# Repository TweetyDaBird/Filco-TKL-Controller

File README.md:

# Filco TKL Replacement Controller
 A QMK compatible drop-in replacement controller

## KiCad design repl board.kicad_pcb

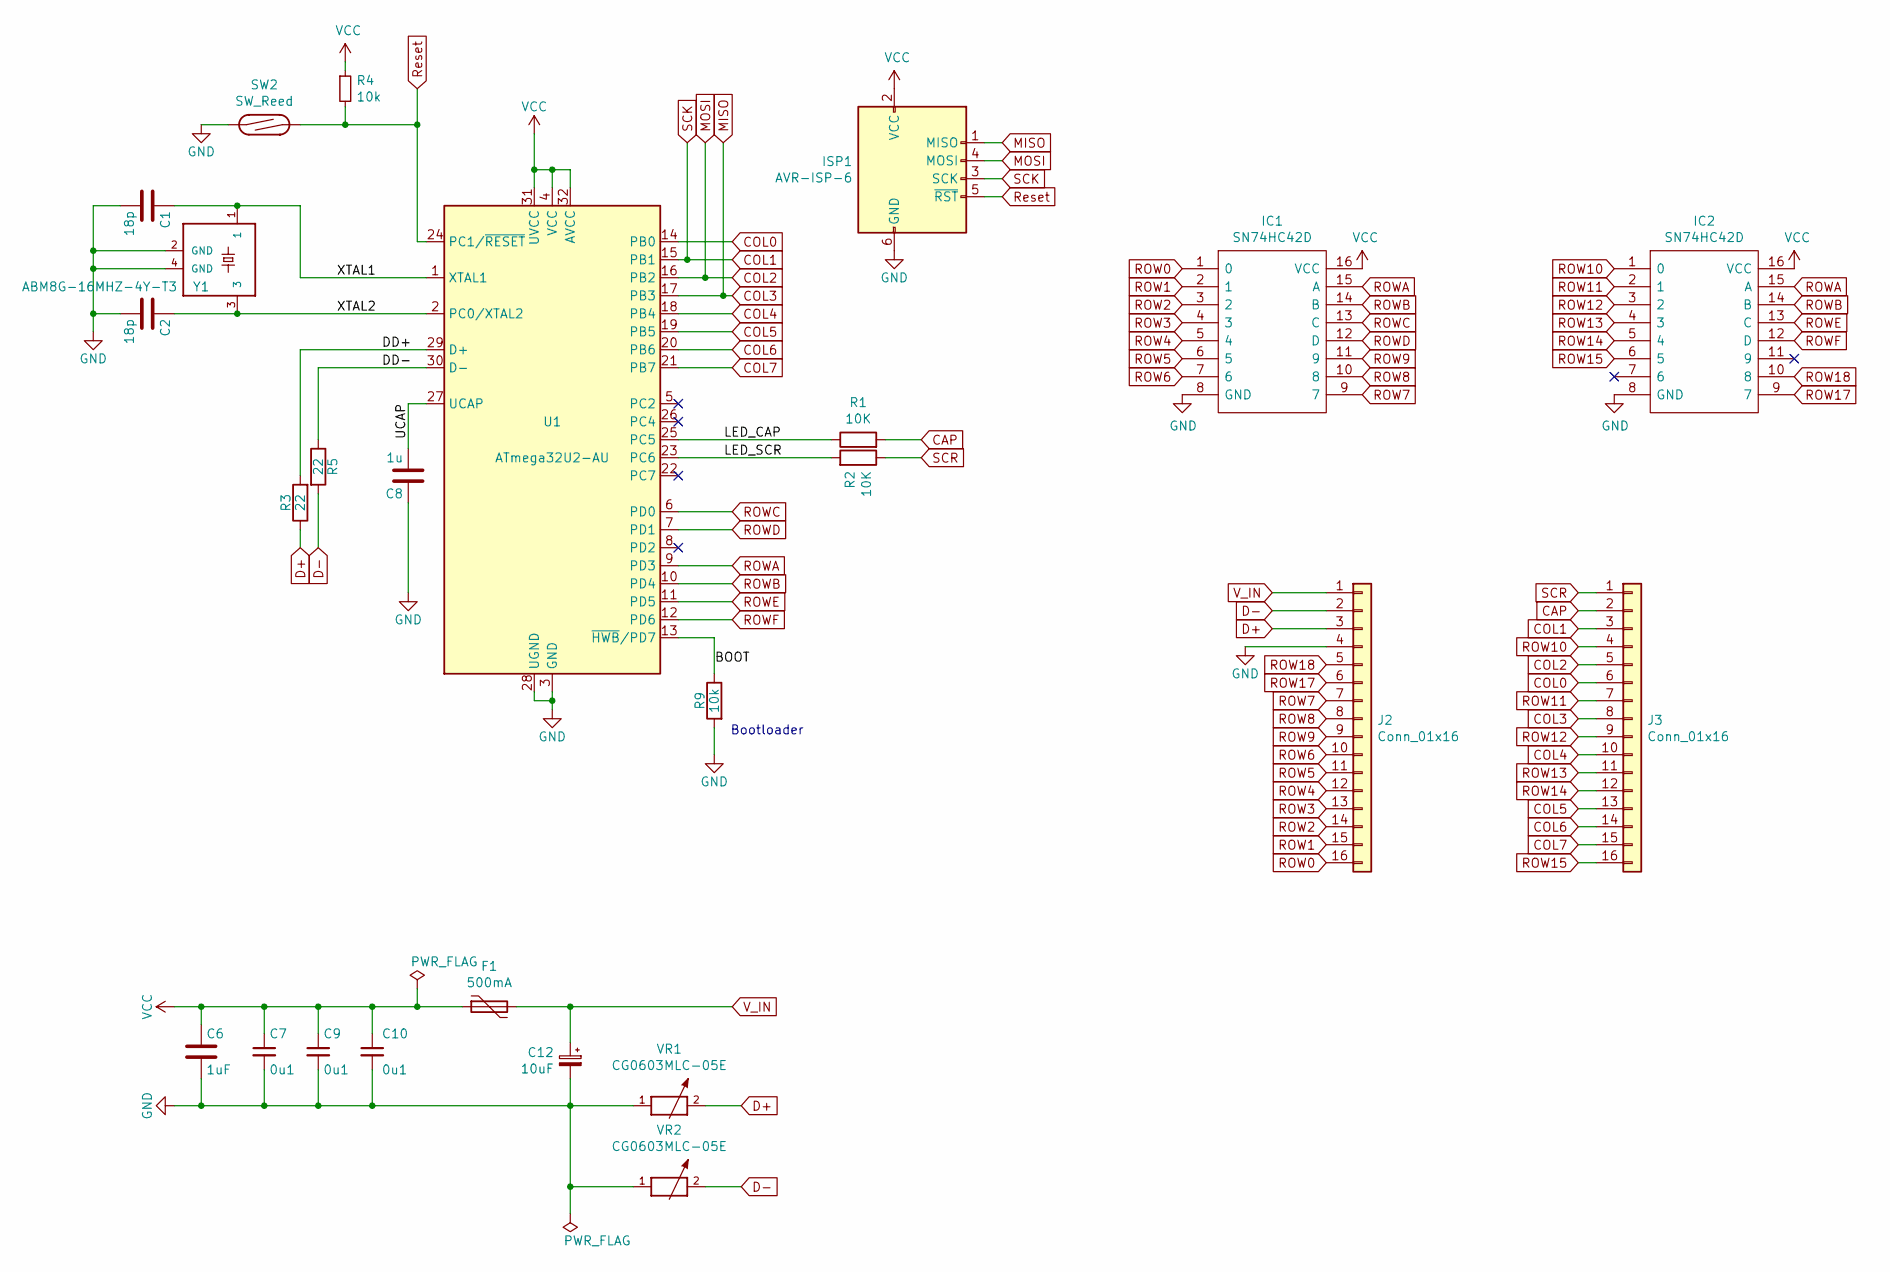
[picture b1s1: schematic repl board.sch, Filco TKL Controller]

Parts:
C1, C2: 18p; C_0603_1608Metric_Pad1.05x0.95mm_HandSolder
C6: 1uF; C_0603_1608Metric_Pad1.05x0.95mm_HandSolder
C7, C9, C10: 0u1; C_0603_1608Metric_Pad1.05x0.95mm_HandSolder
C8: 1u; C_0603_1608Metric_Pad1.05x0.95mm_HandSolder
C12: 10uF; CP_EIA-3216-18_Kemet-A_Pad1.58x1.35mm_HandSolder
F1: 500mA; Fuse_0805_2012Metric_Pad1.15x1.40mm_HandSolder
IC1, IC2: SN74HC42D; SOP-16_4.4x10.4mm_P1.27mm; Manufacturer_Part_Number SN74HC42D; Mouser Part Number 595-SN74HC42D
ISP1: AVR-ISP-6; PinHeader_1x06_P2.54mm_Vertical
J2, J3: Conn_01x16; PinHeader_1x16_P2.00mm_Vertical
R1, R2: 10K; R_0603_1608Metric_Pad1.05x0.95mm_HandSolder
R3, R5: 22; R_0603_1608Metric_Pad1.05x0.95mm_HandSolder
R4, R9: 10k; R_0603_1608Metric_Pad1.05x0.95mm_HandSolder
SW2: SW_Reed; R_Axial_DIN0309_L9.0mm_D3.2mm_P15.24mm_Horizontal
U1: ATmega32U2-AU; TQFP-32_7x7mm_P0.8mm
VR1, VR2: CG0603MLC-05E; R_0603_1608Metric_Pad1.05x0.95mm_HandSolder
Y1: ABM8G-16MHZ-4Y-T3; OSCSC320X250X100N

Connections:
/BOOT: R9.1, U1.13 (~HWB~/PD7)
/DD+: R3.2, U1.29 (D+)
/DD-: R5.1, U1.30 (D-)
/LED_CAP: R1.1, U1.25 (PC5)
/LED_SCR: R2.2, U1.23 (PC6)
/UCAP: C8.2, U1.27 (UCAP)
/XTAL1: C1.1, U1.1 (XTAL1), Y1.1
/XTAL2: C2.1, U1.2 (PC0/XTAL2), Y1.3
CAP: J3.2, R1.2
COL0: J3.6, U1.14 (PB0)
COL1: ISP1.3 (SCK), J3.3, U1.15 (PB1)
COL2: ISP1.4 (MOSI), J3.5, U1.16 (PB2)
COL3: ISP1.1 (MISO), J3.8, U1.17 (PB3)
COL4: J3.10, U1.18 (PB4)
COL5: J3.13, U1.19 (PB5)
COL6: J3.14, U1.20 (PB6)
COL7: J3.15, U1.21 (PB7)
D+: J2.3, R3.1, VR1.2
D-: J2.2, R5.2, VR2.2
GND: C1.2, C2.2, C6.2, C7.2, C8.1, C9.2, C10.2, C12.2, IC1.8 (GND), IC2.8 (GND), ISP1.6 (GND), J2.4, R9.2, SW2.1, U1.3 (GND), U1.28 (UGND), VR1.1, VR2.1, Y1.2 (GND), Y1.4 (GND)
ROW0: IC1.1 (0), J2.16
ROW1: IC1.2 (1), J2.15
ROW2: IC1.3 (2), J2.14
ROW3: IC1.4 (3), J2.13
ROW4: IC1.5 (4), J2.12
ROW5: IC1.6 (5), J2.11
ROW6: IC1.7 (6), J2.10
ROW7: IC1.9 (7), J2.7
ROW8: IC1.10 (8), J2.8
ROW9: IC1.11 (9), J2.9
ROW10: IC2.1 (0), J3.4
ROW11: IC2.2 (1), J3.7
ROW12: IC2.3 (2), J3.9
ROW13: IC2.4 (3), J3.11
ROW14: IC2.5 (4), J3.12
ROW15: IC2.6 (5), J3.16
ROW17: IC2.9 (7), J2.6
ROW18: IC2.10 (8), J2.5
ROWA: IC1.15 (A), IC2.15 (A), U1.9 (PD3)
ROWB: IC1.14 (B), IC2.14 (B), U1.10 (PD4)
ROWC: IC1.13 (C), U1.6 (PD0)
ROWD: IC1.12 (D), U1.7 (PD1)
ROWE: IC2.13 (C), U1.11 (PD5)
ROWF: IC2.12 (D), U1.12 (PD6)
Reset: ISP1.5 (~RST), R4.2, SW2.2, U1.24 (PC1/~RESET)
SCR: J3.1, R2.1
VCC: C6.1, C7.1, C9.1, C10.1, F1.1, IC1.16 (VCC), IC2.16 (VCC), ISP1.2 (VCC), R4.1, U1.4 (VCC), U1.31 (UVCC), U1.32 (AVCC)
V_IN: C12.1, F1.2, J2.1

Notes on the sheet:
Bootloader

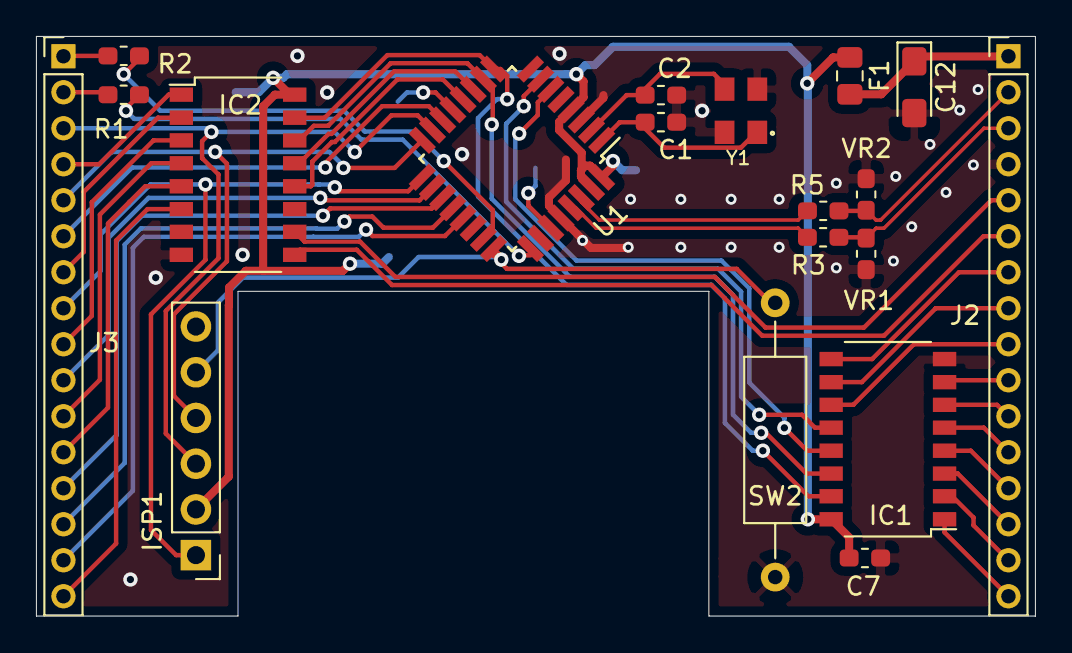
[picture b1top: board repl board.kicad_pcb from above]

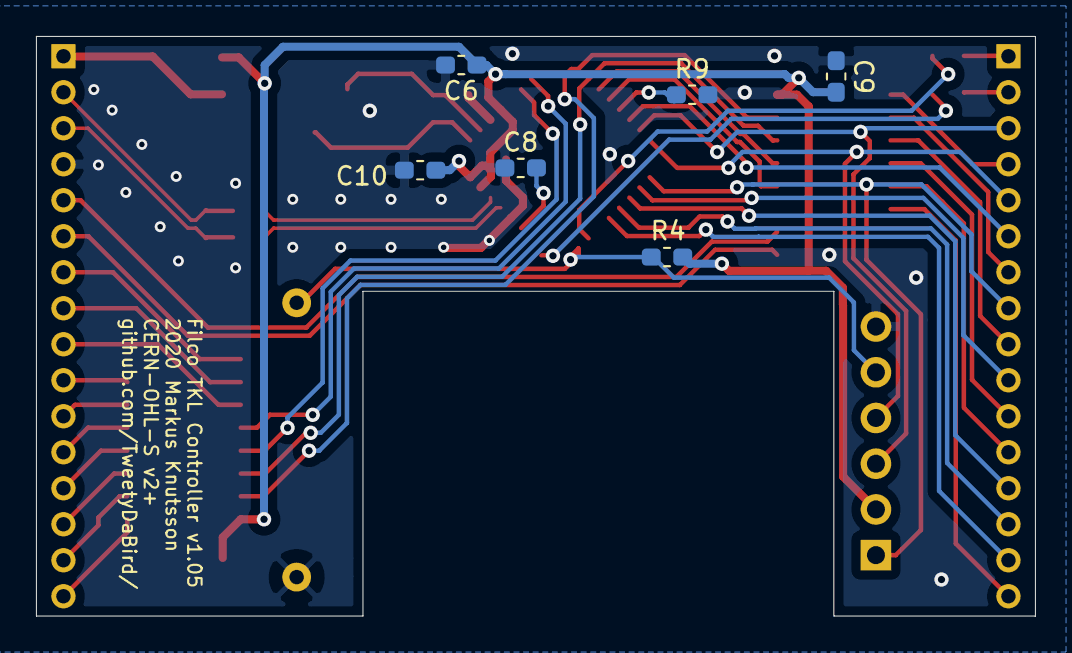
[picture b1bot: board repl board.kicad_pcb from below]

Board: 2 copper layers, 55.5 x 32.2 mm, 25 parts (6 on the bottom side), 48 nets.

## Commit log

2020-09-29 Published v1.0
2020-09-29 Update repl board.sch
    updated licensing to schematic
2020-09-29 removed old backups
2020-10-26 Fix chrystal
    Fix Chrystal footprint, added ICSP header
2020-11-04 v1.05
    Corrected USB D+/D-
2020-11-05 Adjustment for DRC
2020-11-12 Moved files
2020-12-16 cleaned up licence texts

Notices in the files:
repl board.kicad_pcb:
Licensed under CERN-OHL-S v2 or any later version
CERN-OHL-S v2+
